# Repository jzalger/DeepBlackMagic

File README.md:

DeepBlackMagic
==============

This project contains the control software for a custom underwater camera system based on the BlackMagic Micro Cinema Camera (BMMCC).

The controller converts basic momentary control such as recording start/stop and aperature adustments and sends it to the camera via SBUS.

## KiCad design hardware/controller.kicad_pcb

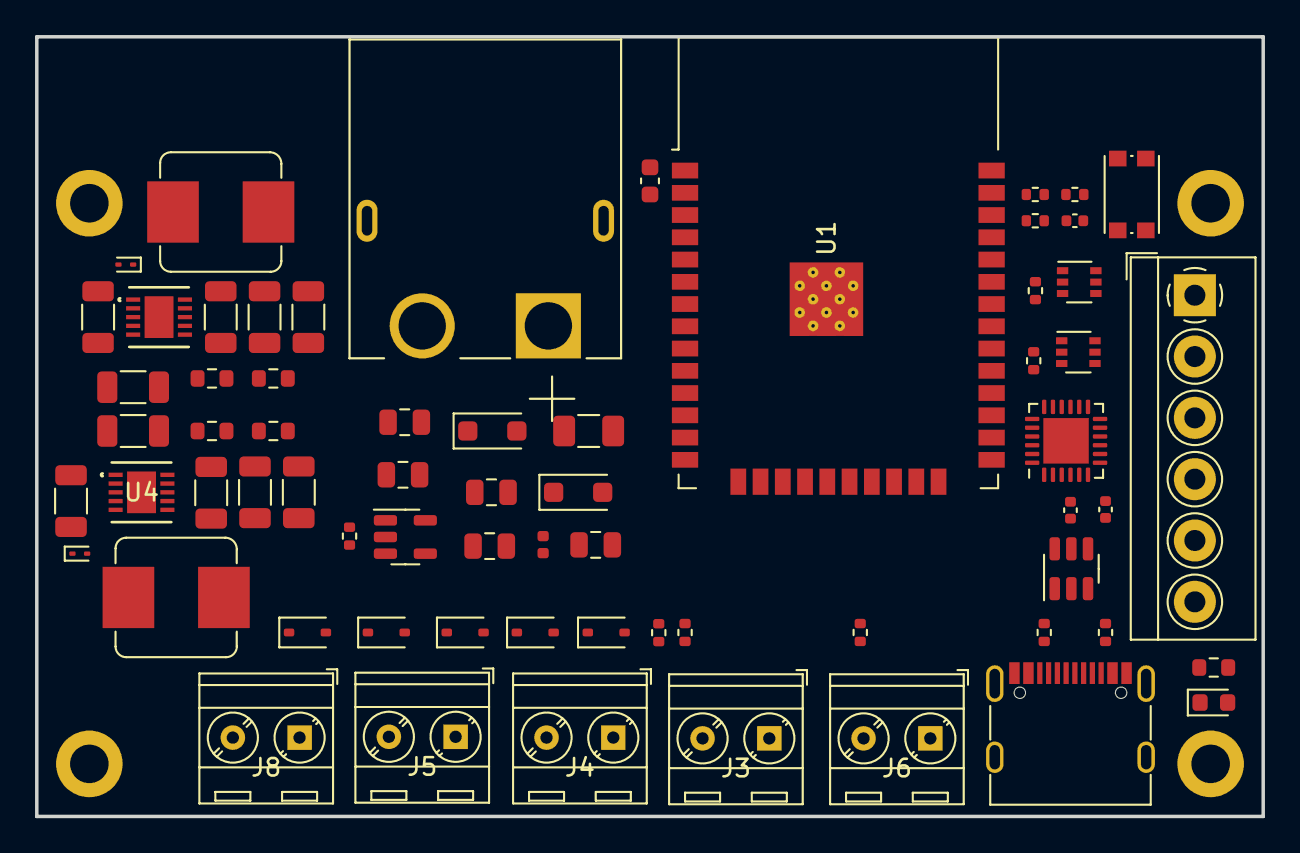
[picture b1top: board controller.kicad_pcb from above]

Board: 4 copper layers, 70.0 x 44.5 mm, 70 parts (0 on the bottom side), 43 nets, no tracks yet.

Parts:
C1: 1uF; C_0402_1005Metric
C2, C3, C4, C5: 22uF; C_1206_3216Metric
C6, C8: 0.1uF; C_1206_3216Metric
C9, C11: 10uF; C_1206_3216Metric
C10, C12: 0.18uF; C_1206_3216Metric
C13: 100nF; C_0402_1005Metric
C14, C15, C18: 1uF; C_0805_2012Metric
C16, C17: 10uF; C_0805_2012Metric
C19: 10uF; C_0603_1608Metric
C20: 10uF; C_0402_1005Metric
D1, D2: 0.32V; D_SOD-923
D3, D10: MBR120; D_SOD-123F
D4: LED; LED_0603_1608Metric
D5, D6, D7, D8, D9: PESD3V3L1BA; D_SOD-323
F1: 2A; Fuse_1206_3216Metric
H1, H2, H3, H4: MountingHole_Pad; MountingHole_2.2mm_M2_DIN965_Pad
J1: USB_C_Receptacle_USB2.0; USB_C_Receptacle_G-Switch_GT-USB-7010ASV
J2: XT60PW-M; AMASS_XT60PW-M
J3: 12V; TerminalBlock_MetzConnect_Type086_RT03402HBLC_1x02_P3.81mm_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
J4: SBUS; TerminalBlock_MetzConnect_Type086_RT03402HBLC_1x02_P3.81mm_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
J5: BTN1; TerminalBlock_MetzConnect_Type086_RT03402HBLC_1x02_P3.81mm_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
J6: SW; TerminalBlock_MetzConnect_Type086_RT03402HBLC_1x02_P3.81mm_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
J7: DNP; TerminalBlock_4Ucon_1x06_P3.50mm_Horizontal
J8: BTN0; TerminalBlock_MetzConnect_Type086_RT03402HBLC_1x02_P3.81mm_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
L1, L2: 3.3uH; L_Bourns_SRP7028A_7.3x6.6mm
L3: 10nH; L_0402_1005Metric
Q1, Q2: MMDT2222A; SOT-363_SC-70-6
R1: 1k; R_0603_1608Metric
R2: 1.02k; R_0603_1608Metric
R3, R4, R5, R7, R11, R14, R15: 10k; R_0402_1005Metric
R6: 11k; R_0603_1608Metric
R8: 2.32k; R_0603_1608Metric
R9: 100k; R_0402_1005Metric
R10: 300; R_0603_1608Metric
R12, R13: 5k1; R_0402_1005Metric
R16: 20k; R_0402_1005Metric
SW1: SW_SPST; SW_Push_1P1T_NO_CK_KMR2
U1: ESP32-WROOM-32
U2: CP2104; QFN-24-1EP_4x4mm_P0.5mm_EP2.6x2.6mm
U3, U4: LMR12020XSD/NOPB; DSC_10_TEX
U5: USBLC6-2SC6; SOT-23-6
U6: AP2112K-3.3; SOT-23-5

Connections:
+3.3V: C3.1, C5.1, C12.2, C17.1, C18.1, C19.1, C20.2, D4.2 (A), J7.1, J8.1, L2.1, R3.1, R8.2, R14.1, R15.1, U1.2 (VDD), U2.5 (VIO), U2.6 (VDD), U2.7 (REGIN), U6.5 (VOUT)
+12V: C2.1, C4.1, C10.2, J3.1, L1.1, R6.2
/MicroController/A0_REC: D6.2 (A2), J8.2, U1.11 (IO26)
/MicroController/A1_AUX_UP: D7.2 (A2), J5.1, U1.10 (IO25)
/MicroController/A5_AUX_DN: D8.2 (A2), J5.2, U1.26 (IO4)
/MicroController/DTR: Q1.1 (E1), R5.1, U2.23 (~DTR)
/MicroController/GPIO0: Q1.6 (C1), U1.25 (IO0)
/MicroController/GPIO2: J7.3, U1.24 (IO2)
/MicroController/IO12_A11: J7.6, U1.14 (IO12)
/MicroController/RESET: C1.1, Q2.6 (C1), R3.2, SW1.2 (B), U1.3 (EN)
/MicroController/RTS: Q2.1 (E1), R4.1, U2.19 (~RTS)
/MicroController/RXDO: U1.34 (RXD0/IO3), U2.21 (TXD)
/MicroController/SBUS_RX_H: D9.2 (A2), J4.1, R7.2
/MicroController/SBUS_RX_L: R7.1, R16.2, U1.27 (IO16)
/MicroController/SBUS_TX: D5.2 (A2), J4.2, U1.28 (IO17)
/MicroController/SCL: J7.4, R14.2, U1.36 (IO22)
/MicroController/SDA: J7.5, R15.2, U1.37 (IO23)
/MicroController/TXDO: U1.35 (TXD0/IO1), U2.20 (RXD)
/MicroController/USB_CON_D+: J1.A6 (D+), J1.B6 (D+), U5.3 (I/O2)
/MicroController/USB_CON_D-: J1.A7 (D-), J1.B7 (D-), U5.1 (I/O1)
/MicroController/USB_D+: U2.3 (D+), U5.4 (I/O2)
/MicroController/USB_D-: U2.4 (D-), U5.6 (I/O1)
/Power/3V_BUCK_SW: C8.1, D2.1 (K), L2.2, U4.1 (SW), U4.2 (SW)
/Power/3V_SW_FB: C12.1, R2.1, R8.1, U4.6 (FB)
/Power/12V_BUCK_SW: C6.1, D1.1 (K), L1.2, U3.1 (SW), U3.2 (SW)
/Power/12V_SW_FB: C10.1, R1.1, R6.1, U3.6 (FB)
/Power/PWR_ENABLE: R11.2, U3.4 (EN), U4.4 (EN)
GND: C1.2, C2.2, C3.2, C4.2, C5.2, C9.2, C11.2, C13.2, C14.2, C15.2, C16.2, C17.2, C18.2, C19.2, C20.1, D1.2 (A), D2.2 (A), D5.1 (A1), D6.1 (A1), D7.1 (A1), D8.1 (A1), D9.1 (A1), H1.1, H2.1, H3.1, H4.1, J1.A1 (GND), J1.A12 (GND), J1.B1 (GND), J1.B12 (GND), J1.S1 (SHIELD), J2.2 (-), J3.2, J7.2, R1.2, R2.2, R10.2, R12.1, R13.2, R16.1, SW1.1 (A), U1.1 (GND), U1.15 (GND), U1.38 (GND), U1.39 (GND), U2.2 (GND), U2.25 (GND), U3.7 (GND), U3.11 (EPAD), U4.7 (GND), U4.11 (EPAD), U5.2 (GND), U6.2 (GND)
unnamed: D3.2 (A), F1.1
unnamed: D4.1 (K), R10.1
unnamed: C14.1, D10.1 (K), L3.1
unnamed: J1.A5 (CC1), R12.2
unnamed: J1.B5 (CC2), R13.1
unnamed: F1.2, J2.1 (+)
unnamed: J6.2, R11.1
unnamed: Q1.2 (B1), R4.2
unnamed: Q2.2 (B1), R5.2
unnamed: C6.2, U3.3 (BOOST)
unnamed: C8.2, U4.3 (BOOST)
unnamed: R9.2, U6.3 (EN)
unnamed: C15.1, C16.1, L3.2, R9.1, U6.1 (VIN)
VBATT: C9.1, C11.1, D3.1 (K), J6.1, U3.8 (AVIN), U3.9 (PVIN), U3.10 (PVIN), U4.8 (AVIN), U4.9 (PVIN), U4.10 (PVIN)
VBUS: C13.1, D10.2 (A), J1.A4 (VBUS), J1.A9 (VBUS), J1.B4 (VBUS), J1.B9 (VBUS), U2.8 (VBUS), U5.5 (VBUS)

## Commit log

2023-04-01 sbus and button implementation
2023-04-02 Changed GPIO pins and improved button press stability.
2023-04-02 Fixed SBUS channel alignment
2023-04-02 Added CI configuration
2023-04-02 Doc updates
2023-04-02 readme updates
2023-04-02 CI Fixes
2023-04-02 Refactoring
2023-04-03 Fixed SBUS issues with camera [not tested]
2023-04-04 Fixed recording control
2023-04-04 Working camera control
2023-05-20 Initial hardware files
2023-05-20 Rouging out schematic
2023-06-03 Schematic updates and initial layout
